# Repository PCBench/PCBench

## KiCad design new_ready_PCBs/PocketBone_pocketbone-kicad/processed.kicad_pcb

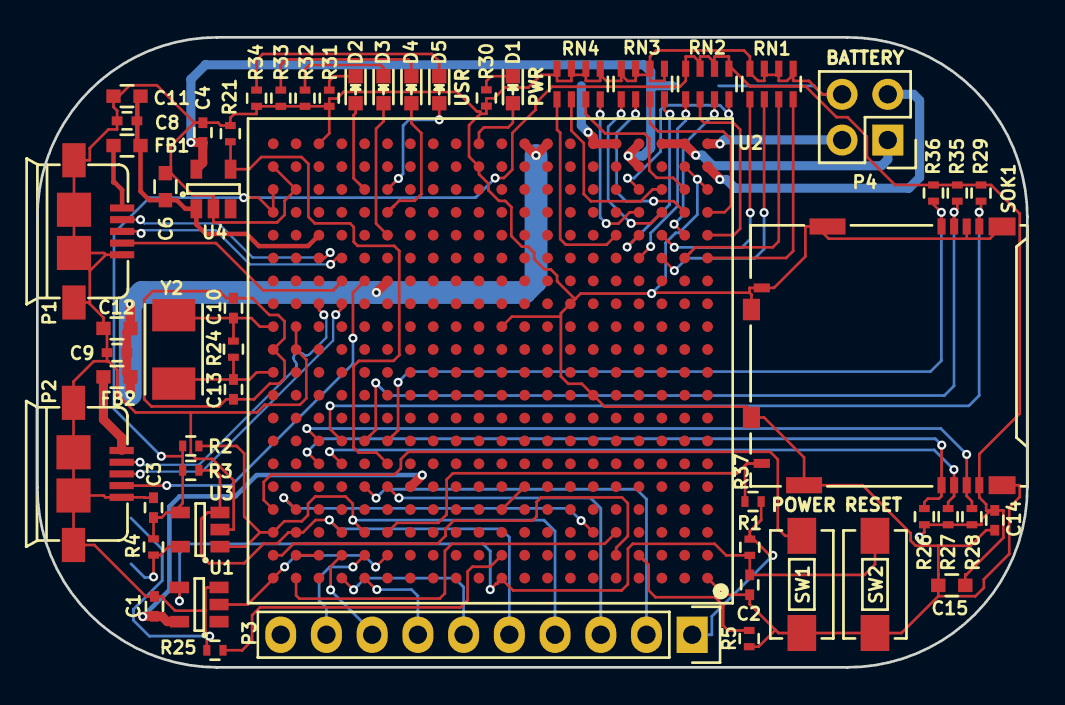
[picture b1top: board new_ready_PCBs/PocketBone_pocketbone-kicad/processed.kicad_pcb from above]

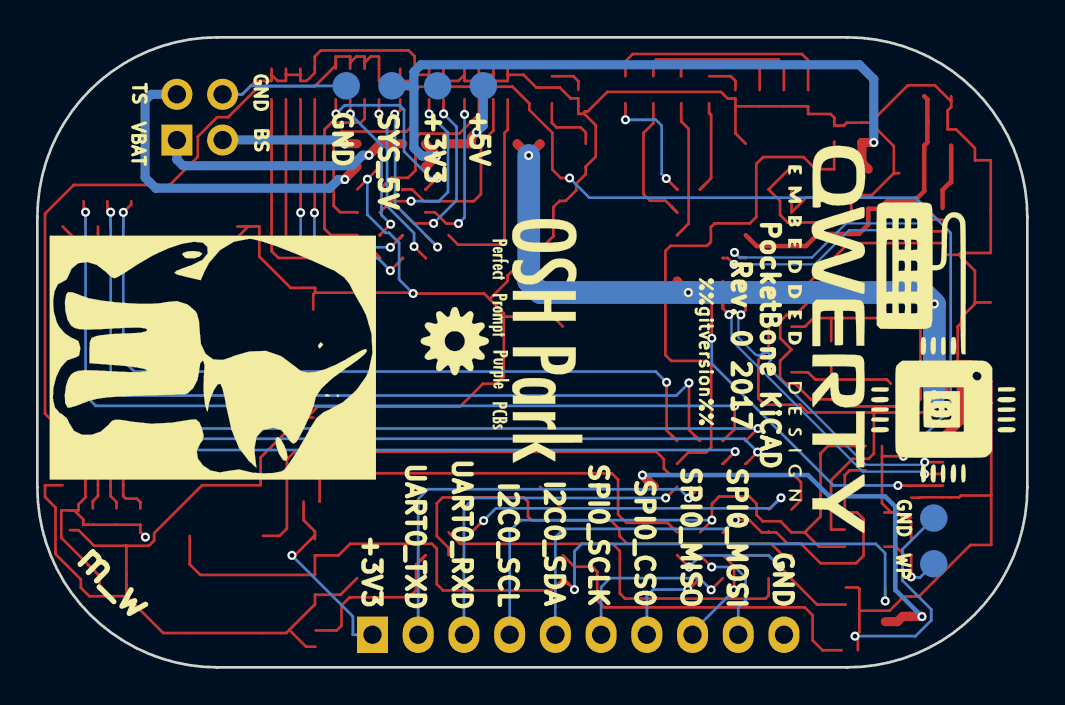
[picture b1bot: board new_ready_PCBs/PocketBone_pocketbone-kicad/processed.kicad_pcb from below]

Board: 4 copper layers, 55.0 x 35.0 mm, 62 parts (6 on the bottom side), 74 nets.

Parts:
C1, C3, C4, C8, C9, C14: 0.1uF; C_0402
C2: 1uF; C_0402
C6, C11, C12, C15: 10uF; C_0603
C10, C13: 18pF; C_0402
D1, D2, D3, D4, D5: BLUE; LED-0603
FB1, FB2: FILTER; C_0603
P1, P2: USB_OTG; USB_MICRO_B_ST-USB-001E
P3: CONN_01X10; Socket_Strip_Straight_1x10
P4: CONN_02X02; Socket_Strip_Straight_2x02
R1, R5, R26, R27, R28, R29, R35, R36, R37: 10K; R_0402
R2, R3, R4: 1.5K; R_0402
R21: 100K; R_0402
R24: 1M; R_0402
R25: 4.87K; R_0402
R30: 4.7K; R_0402
R31, R32, R33, R34: 240; R_0402
RN1, RN2, RN3, RN4: 100K; R_Array_Concave_4x0603
SOK1: SCHA5B0200
SW1, SW2: SW_PUSH_SMALL_H; SW_SPST_EVQPE1
TP1: 5V; Measurement_Point_Round-SMD-Pad_Small
TP2: WP; Measurement_Point_Round-SMD-Pad_Small
TP3, TP6: GND; Measurement_Point_Round-SMD-Pad_Small
TP4: 3P3; Measurement_Point_Round-SMD-Pad_Small
TP5: SYS_5V; Measurement_Point_Round-SMD-Pad_Small
U1: SN74LVC1G07; SOT-23-5
U2: OSD3358; BGA-400-1-27mm
U3: 24LC32AT-I/OT; SOT-23-5
U4: TPS2051C; SOT-23-5
Y2: 24MHz; 445C33D24M00000

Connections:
3P3AUX: D1.2, U2.Y11
+3V3: C3.1, C14.1, C15.1, P3.1, R1.1, R2.1, R3.1, R4.1, R26.1, R27.1, R28.1, R29.1, R35.1, R36.1, R37.1, RN2.5, RN2.6, RN2.7, RN2.8, SOK1.4, U2.U20, U2.V20, U3.4
+5V: TP1.1, U2.Y5, U2.Y6
BAT_SENSE: P4.3, U2.Y1
GND: C1.2, C2.2, C3.2, C4.2, C6.2, C8.2, C9.2, C11.2, C12.2, C14.2, C15.2, P1.5, P1.6, P1.7, P1.8, P1.9, P2.5, P2.6, P2.7, P2.8, P2.9, P3.10, P4.4, R5.2, R21.2, R25.1, R30.1, R31.1, R32.1, R33.1, R34.1, RN1.1, RN1.2, RN1.3, RN1.4, RN3.1, RN3.2, RN3.3, RN3.4, RN4.1, RN4.2, RN4.3, RN4.4, SOK1.6, SOK1.10, SOK1.11, SW1.1, SW2.1, TP3.1, TP6.1, U1.3, U2.A1, U2.J6, U2.L19, U2.M10, U2.M19, U2.N7, U2.V1, U2.V19, U2.W2, U2.W11, U2.W20, U2.Y18, U3.2, U4.2
I2C0_SCL: P3.4, R2.2, U2.C16, U2.C20, U3.1
I2C0_SDA: P3.5, R3.2, U2.C17, U2.C19, U3.3
MMC0_CD: R37.2, SOK1.9, U2.C15
MMC0_CLK: R29.2, SOK1.5, U2.G17
MMC0_CMD: R28.2, SOK1.3, U2.G18
MMC0_DAT0: R35.2, SOK1.7, U2.G16
MMC0_DAT1: R36.2, SOK1.8, U2.G15
MMC0_DAT2: R26.2, SOK1.1, U2.F18
MMC0_DAT3: R27.2, SOK1.2, U2.F17
unnamed: C2.1, R1.2, SW2.2, U1.4, U2.A10
unnamed: C10.1, R24.2, U2.M20, Y2.1
unnamed: C13.1, R24.1, U2.K20, Y2.2
unnamed: D1.1, R30.2
unnamed: D2.1, R31.2
unnamed: D3.1, R32.2
unnamed: D4.1, R33.2
unnamed: D5.1, R34.2
unnamed: FB1.2, P1.1
unnamed: FB2.2, P2.1
unnamed: R4.2, TP2.1, U3.5
unnamed: R5.1, U2.B4
unnamed: RN1.5, U2.T3
unnamed: RN1.6, U2.R3
unnamed: RN1.7, U2.R2
unnamed: RN1.8, U2.R1
unnamed: RN2.1, U2.R4
unnamed: RN2.2, U2.T1
unnamed: RN2.3, U2.T2
unnamed: RN2.4, U2.V4
unnamed: RN3.5, U2.U3
unnamed: RN3.6, U2.U2
unnamed: RN3.7, U2.U1
unnamed: RN3.8, U2.T4
unnamed: RN4.5, U2.T5
unnamed: RN4.6, U2.V3
unnamed: RN4.7, U2.V2
unnamed: RN4.8, U2.U4
unnamed: SW1.2, U2.D20
unnamed: U2.A19, U2.C5
unnamed: U2.B18, U2.B19
unnamed: U2.B5, U2.B20
unnamed: U2.C6, U2.D19
OSC0_GND: C10.2, C13.2, U2.L20
PMIC_PGOOD: U1.2, U2.A20, U2.B15
SPI_CLK: P3.6, U2.A17
SPI_CS0: P3.7, U2.A16
SPI_MISO: P3.8, U2.B17
SPI_MOSI: P3.9, U2.B16
SYS_5V: C4.1, TP5.1, U2.W4, U2.Y4, U4.5
TRSTN: R25.2, U2.B10
TS: P4.2, U2.W1
UART0_RXD: P3.3, U2.E15
UART0_TXD: P3.2, U2.E16
USB0_D_N: P2.2, U2.N18
USB0_D_P: P2.3, U2.N17
USB0_ID: P2.4, U2.P16
USB0_VBUS: C9.1, C12.1, FB2.1, U2.P15, U2.Y8, U2.Y9
USB1_DRVVBUS: R21.1, U2.F15, U4.4
USB1_D_N: P1.2, U2.R18
USB1_D_P: P1.3, U2.R17
USB1_ID: P1.4, U2.P17
USB1_VBUS: C6.1, C8.1, C11.1, FB1.1, U2.T18, U4.1
USR0_LED: D5.2, U2.V15
USR1_LED: D4.2, U2.U15
USR2_LED: D3.2, U2.T15
USR3_LED: D2.2, U2.V16
VBAT: P4.1, U2.Y2, U2.Y3
VDD_1V8: U2.D10, U2.E9
VDD_RTC: C1.1, U1.5, U2.E14

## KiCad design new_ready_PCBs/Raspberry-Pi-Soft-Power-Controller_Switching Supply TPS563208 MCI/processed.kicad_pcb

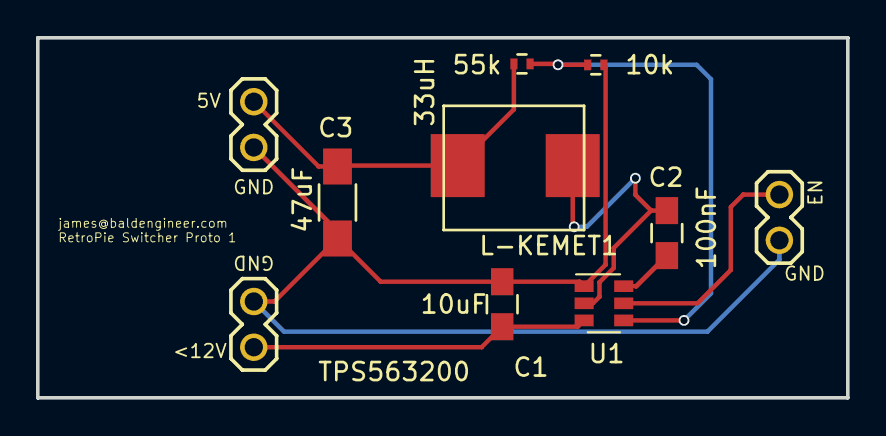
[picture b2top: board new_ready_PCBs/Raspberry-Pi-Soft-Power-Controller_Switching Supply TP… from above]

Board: 2 copper layers, 45.0 x 20.0 mm, 10 parts (0 on the bottom side), 7 nets.

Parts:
C1: 10uF; C_0805_HandSoldering
C2: 100nF; C_0805_HandSoldering
C3: 47uF; C_1206_HandSoldering
J1: 9V-IN; 1X02
J2: EN; 1X02
J3: 5V-OUT; 1X02
L-KEMET1: 33uH; KT-MPLCH-0740-Hand
R1: 55k; R_0402
R2: 10k; R_0402
U1: TPS563200; SOT-23-6

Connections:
/ENABLE: J2.2, U1.5
/IN: C1.1, J1.2, U1.3
/OUT: C3.2, J3.1, L-KEMET1.2, R1.1
/ToCoil: C2.1, L-KEMET1.1, U1.2
GND: C1.2, C3.1, J1.1, J2.1, J3.2, R2.2, U1.1
unnamed: C2.2, U1.6
unnamed: R1.2, R2.1, U1.4

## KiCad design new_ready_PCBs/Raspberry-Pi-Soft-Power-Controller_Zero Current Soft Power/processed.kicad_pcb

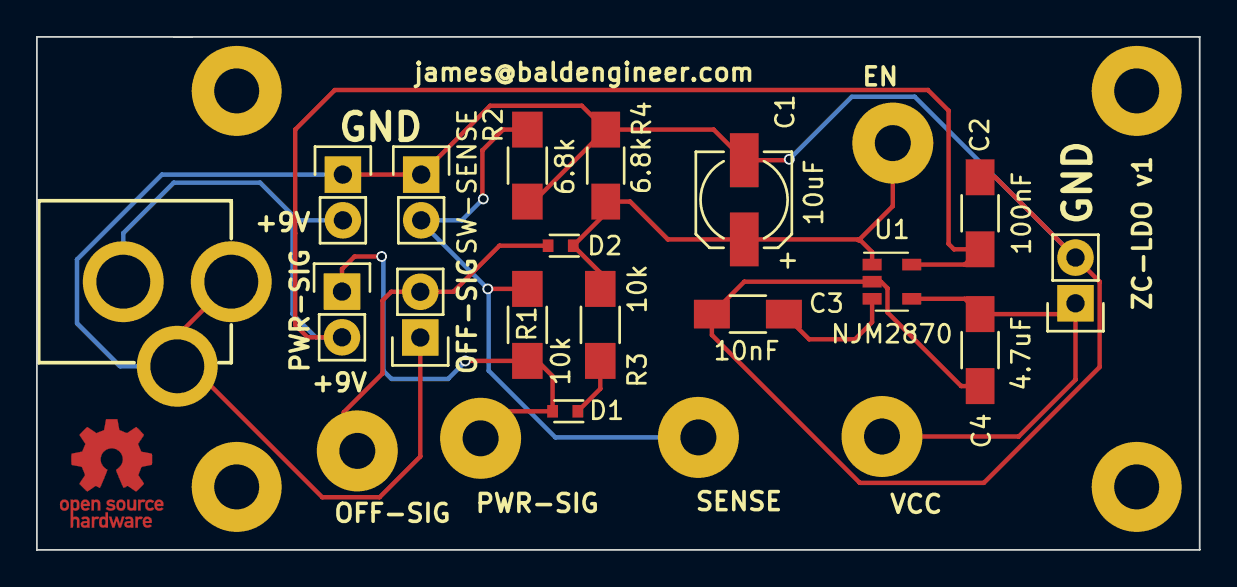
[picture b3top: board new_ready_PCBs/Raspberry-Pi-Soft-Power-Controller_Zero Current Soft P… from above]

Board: 2 copper layers, 64.6 x 28.5 mm, 22 parts (0 on the bottom side), 9 nets.

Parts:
C1: 10uF; c_elec_5x5.3
C2: 100nF; C_1206_HandSoldering
C3: 10nF; C_1206_HandSoldering
C4: 4.7uF; C_1206_HandSoldering
D1, D2: 1SS389; SOD-523
J1: PWR-SIG; Pin_Header_Straight_1x02
J2: SW-SENSE; Pin_Header_Straight_1x02
J3: 9V-IN; Pin_Header_Straight_1x02
J4: SENSE; SolderWirePad_single_2mmDrill
J5: OFF-SIG; Pin_Header_Straight_1x02
J6: TEST_1P; SolderWirePad_single_2mmDrill
J7: OFF-SIG; SolderWirePad_single_2mmDrill
J8: EN; SolderWirePad_single_2mmDrill
J9: VCC; SolderWirePad_single_2mmDrill
J10: AVR-VCC; Pin_Header_Straight_1x02
J11: 9V-BJ; POWER_JACK_PTH
R1, R3: 10k; R_1206_HandSoldering
R2: 6.8k; R_1206_HandSoldering
R4: 6.8k; C_1206_HandSoldering
U1: NJM2870; SOT-23-5

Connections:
+9V: C2.1, J1.2, J3.2, J11.1, U1.5
/LC-VCC: C4.1, J9.1, J10.1, U1.4
/OFF-SIG: D2.2, J5.2, J7.1
/PWR-SIG: D1.2, J1.1, J6.1, R1.2
/SW-SENSE: J2.2, J4.1, R1.1, R2.2
GND: C1.2, C2.2, C3.2, C4.2, J2.1, J3.1, J5.1, J10.2, J11.2, J11.3, R2.1, R4.1, U1.2
unnamed: C1.1, D2.1, J8.1, R3.1, R4.2, U1.1
unnamed: C3.1, U1.3
unnamed: D1.1, R3.2

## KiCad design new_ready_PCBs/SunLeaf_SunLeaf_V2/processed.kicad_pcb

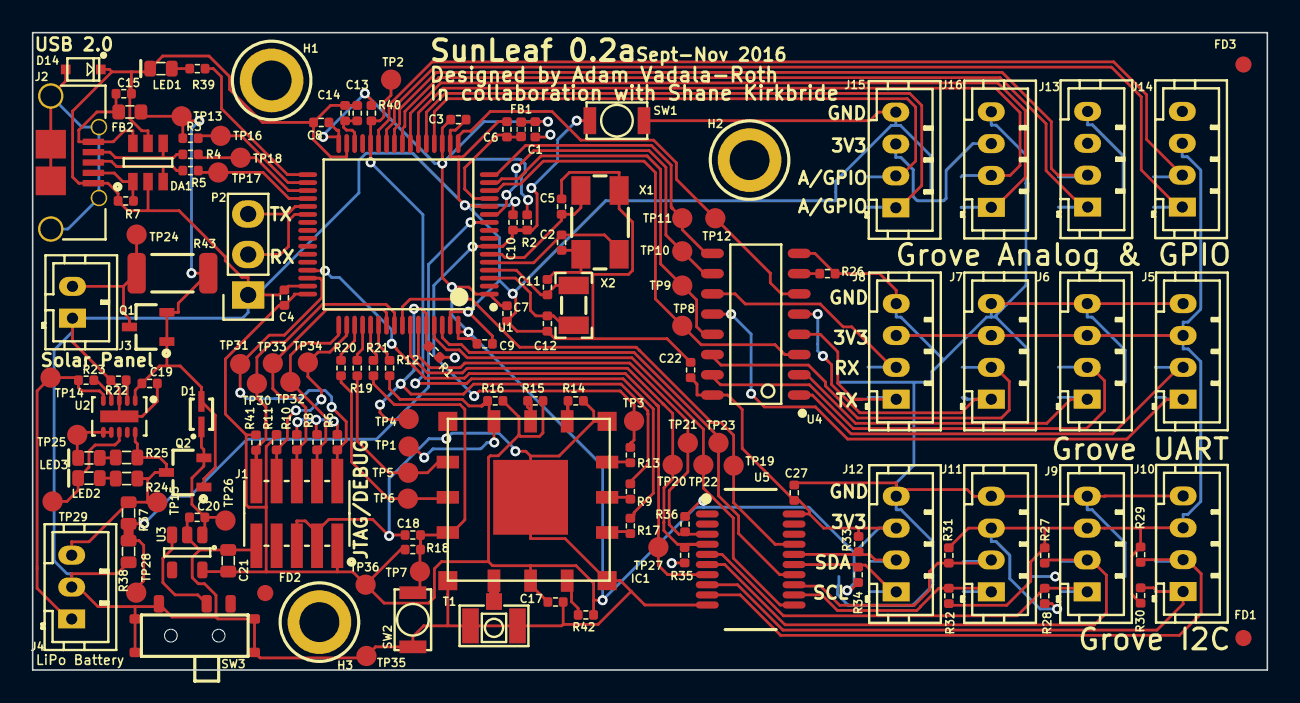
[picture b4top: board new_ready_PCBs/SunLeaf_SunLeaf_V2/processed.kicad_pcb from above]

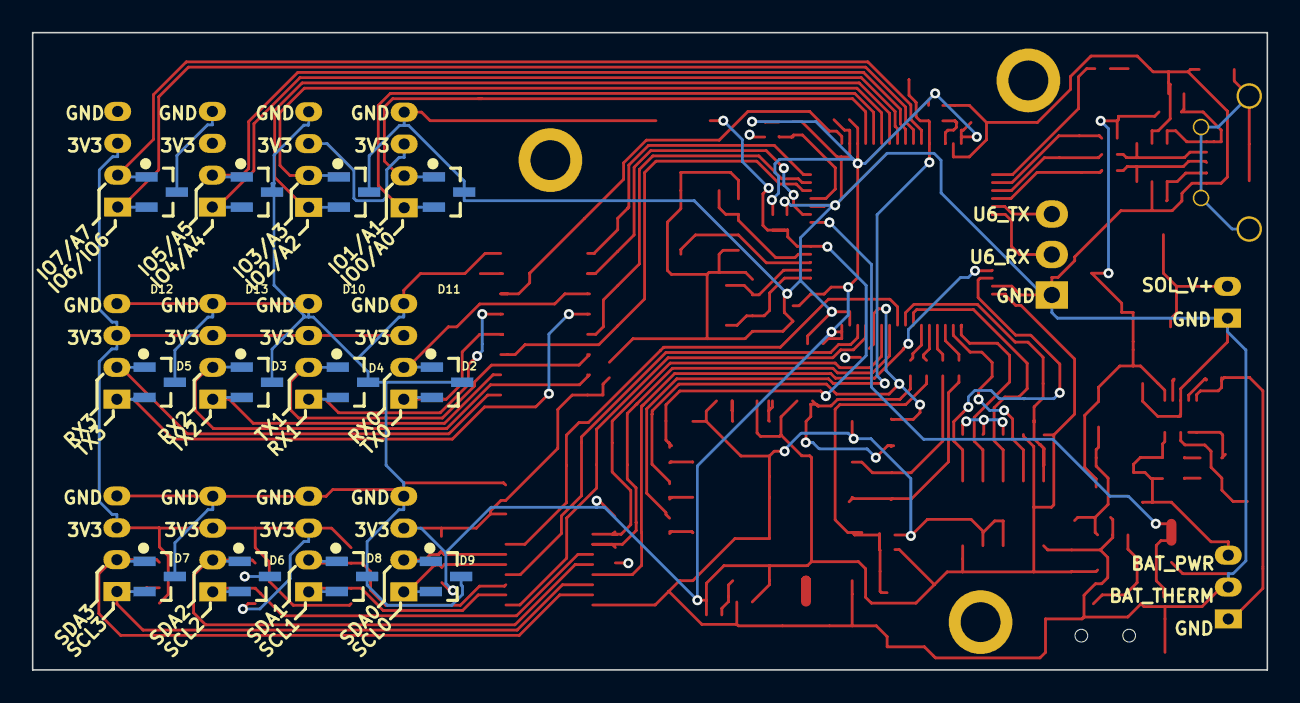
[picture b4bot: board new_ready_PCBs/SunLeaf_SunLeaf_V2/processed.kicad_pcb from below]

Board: 4 copper layers, 77.5 x 40.0 mm, 158 parts (12 on the bottom side), 92 nets.

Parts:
C1, C3, C4, C6, C7, C8, C9, C10, C14, C15, C17, C18, C22, C27: CL05B104JP5NNNC; C0402
C2, C5: CL05C090CB5NNNC; C0402
C11, C12: CL05C180GB5NCNC; C0402
C13: CL05A475KQ5NRNC; C0402
C19, C20: CL05A105KA5NQNC; C0402
C21: CL10A106KQ8NNNC; C0603
D1: BAT20JFILM
D2, D3, D4, D5, D6, D7, D8, D9, D10, D11, D12, D13: PESD3V3L2BT,215
D14: RSB39VTE-17
DA1: ESDA6V1BC6
FB1: BLM15HG601SN1D
FB2: MI0603K300R-10
FD1, FD2, FD3: FIDUCIAL
H1, H2, H3: M2.5_Hole; M2.5_HOLE
IC1: ESP_09; ESP-09
J1: 20021121-00010C4LF
J2: 0475890001-MicroUSBPort; 0475890001
J3: B2B-PH-K-S(LF)(SN)
J4: B3B-PH-K-S(LF)(SN)
J5, J6, J7, J8, J9, J10, J11, J12, J13, J14, J15, J16: B4B-PH-K-S(LF)(SN)
LED1: LTST-C193TBKT-5A; LED0603
LED2: LTST-C191KGKT; LED0603
LED3: LTST-C191KFKT; LED0603
P2: CONN_01X03; Pin_Header_Straight_1x03
Q1, Q2: DMG2307L-7
R1, R3, R14, R15, R16, R40, R42: RC1005F103CS; R0402
R2, R6, R8, R10, R11, R18, R23, R26, R39, R41: RC1005F102CS; R0402
R4, R5: CPF0402B22RE1; R0402
R7: RC1005J473CS; R0402
R9, R12, R13, R17, R19, R20, R21: RC1005F201CS; R0402
R22: RC1005F4870CS; R0402
R24, R25: RC1608J202CS; R0603
R27, R28, R29, R30, R31, R32, R33, R34, R35, R36: RC1005F472CS; R0402
R37, R38: ERA-3AEB3741V; R0603
R43: RC5025J000CS; R2010
SW1, SW2: B3U-1000P
SW3: CUS-12TB
T1: 1909763-1
TP1, TP2, TP3, TP4, TP5, TP6, TP7, TP8, TP9, TP10, TP11, TP12, TP13, TP14, TP15, TP16, TP17, TP18, TP19, TP20, TP21, TP22, TP23, TP24, TP25, TP26, TP27, TP28, TP29, TP30, TP31, TP32, TP33, TP34, TP35, TP36: TEST_POINT
U1: STM32F446RET6_-_TQFP64; STM32F446RET6
U2: BQ24210DQCT; BQ24210
U3: AP2112K-3.3TRG1
U4: 74HC4052D
U5: PCA9518DBQR
X1: ABM3B8.000MHZB2T
X2: ABS07-32.768KHZ-9-T

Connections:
+3V3: C1.1, C3.1, C4.1, C7.1, C8.1, C9.1, C17.1, C21.1, C22.1, C27.1, FB1.1, IC1.15, J1.1, J5.3, J6.3, J7.3, J8.3, J9.3, J10.3, J11.3, J12.3, J13.3, J14.3, J15.3, J16.3, R2.1, R6.1, R8.1, R10.1, R11.1, R15.1, R16.1, R18.1, R27.1, R28.1, R29.1, R30.1, R31.1, R32.1, R33.1, R34.1, R35.1, R36.1, R40.1, R41.1, R42.2, TP36.1, U1.1, U1.19, U1.32, U1.48, U1.64, U3.5, U4.16, U5.20
/Analog and Digital Grove IO/ANIO_0: D13.1, J13.2, U1.25
/Analog and Digital Grove IO/ANIO_1: D13.2, J13.1, U1.24
/Analog and Digital Grove IO/ANIO_2: D12.1, J14.2, U1.27
/Analog and Digital Grove IO/ANIO_3: D12.2, J14.1, U1.26
/Analog and Digital Grove IO/ANIO_4: D11.1, J15.2, U1.20
/Analog and Digital Grove IO/ANIO_5: D11.2, J15.1, U1.21
/Analog and Digital Grove IO/ANIO_6: D10.1, J16.2, U1.22
/Analog and Digital Grove IO/ANIO_7: D10.2, J16.1, U1.23
/I2C Grove Sensors/EN1_IMUX: TP27.1, U1.45, U5.7
/I2C Grove Sensors/EN2_IMUX: TP22.1, U1.61, U5.11
/I2C Grove Sensors/EN3_IMUX: TP23.1, U1.62, U5.14
/I2C Grove Sensors/EN4_IMUX: TP19.1, U1.57, U5.17
/I2C Grove Sensors/I2C_SCL: R35.2, TP20.1, U1.58, U5.4
/I2C Grove Sensors/I2C_SDA: R36.2, TP21.1, U1.59, U5.3
/MCU-STM32F446RET6/BAT_VOLT: R37.2, R38.1, TP28.1, U1.10
/MCU-STM32F446RET6/ESPTOST_BOOT0: R1.1, R9.1, TP4.1, U1.60
/MCU-STM32F446RET6/ESPTOST_BOOT1: R17.1, R40.2, TP2.1, U1.28
/MCU-STM32F446RET6/ESP_PGM_MODE: R12.1, U1.54
/MCU-STM32F446RET6/ESP_ST_RST: C10.1, R2.2, R13.1, SW1.1, TP3.1, U1.7
/MCU-STM32F446RET6/ESP_URX: R19.2, U1.52
/MCU-STM32F446RET6/ESP_UTX: R20.2, U1.51
/MCU-STM32F446RET6/HEARTBEAT: R39.1, U1.33
/MCU-STM32F446RET6/NJTRST: J1.10, R41.2, TP30.1, U1.56
/MCU-STM32F446RET6/STM_ESP_RST: R21.2, U1.53
/MCU-STM32F446RET6/SWCLK_TCK: J1.4, R8.2, TP32.1, U1.49
/MCU-STM32F446RET6/SWDIO_TMS: J1.2, R6.2, TP31.1, U1.46
/MCU-STM32F446RET6/SWO_TDI: J1.8, R11.2, TP34.1, U1.50
/MCU-STM32F446RET6/SWO_TDO: J1.6, R10.2, TP33.1, U1.55
/MCU-STM32F446RET6/UART6_RX: P2.2, U1.38
/MCU-STM32F446RET6/UART6_TX: P2.3, U1.37
/MCU-STM32F446RET6/UART_S_RX: TP9.1, U1.15, U4.13
/MCU-STM32F446RET6/USW_EN: TP12.1, U1.17, U4.6
/MCU-STM32F446RET6/USW_S0: TP10.1, U1.11, U4.10
/MCU-STM32F446RET6/USW_S1: TP11.1, U1.16, U4.9
/MCU-STM32F446RET6/VBUS: C19.1, D1.1, FB2.1, Q1.1, Q1.2, Q2.1, R3.2, R43.2, TP13.1, U2.1
/Power-System/BAT: J4.3, Q2.3, R24.2, R25.2, R37.1, TP15.1, U2.10
/Power-System/THERM: J4.1, R23.2, TP14.1, U2.5
/UART Grove Sensors/UART_RX0: D5.1, J5.2, U4.1
/UART Grove Sensors/UART_RX1: D4.1, J6.2, U4.14
/UART Grove Sensors/UART_RX2: D3.1, J7.2, U4.15
/UART Grove Sensors/UART_RX3: D2.1, J8.2, U4.11
/UART Grove Sensors/UART_S_RX: TP8.1, U1.14, U4.3
/UART Grove Sensors/UART_TX0: D5.2, J5.1, U4.12
/UART Grove Sensors/UART_TX1: D4.2, J6.1, U4.5
/UART Grove Sensors/UART_TX2: D3.2, J7.1, U4.2
/UART Grove Sensors/UART_TX3: D2.2, J8.1, U4.4
/WiFi-ESP8266-ESP-09/ANTENNA: IC1.14, T1.1
/WiFi-ESP8266-ESP-09/PGM_MODE: IC1.8, R12.2, R16.2, TP1.1
GND: C1.2, C2.2, C3.2, C4.2, C5.2, C6.2, C7.2, C8.2, C9.2, C10.2, C11.2, C12.2, C13.2, C14.2, C15.1, C17.2, C18.2, C19.2, C20.2, C21.2, C22.2, C27.2, D2.3, D3.3, D4.3, D5.3, D7.3, D8.3, D9.3, D10.3, D11.3, D12.3, D13.3, D14.2, DA1.2, DA1.5, IC1.1, IC1.5, IC1.9, IC1.13, IC1.17, J1.3, J1.5, J1.9, J2.5, J3.1, J4.2, J5.4, J6.4, J7.4, J8.4, J9.4, J10.4, J11.4, J12.4, J13.4, J14.4, J15.4, J16.4, LED1.2, P2.1, R1.2, R7.2, R14.2, R22.2, R26.1, R38.2, SW1.2, SW2.2, SW3.1, SW3.4, T1.2, TP35.1, U1.12, U1.18, U1.31, U1.47, U1.63, U2.3, U2.11, U3.2, U4.8, U5.10, X1.2, X1.4
unnamed: C2.1, U1.5, X1.1
unnamed: C5.1, U1.6, X1.3
unnamed: C6.1, FB1.2, U1.13
unnamed: C11.1, U1.4, X2.1
unnamed: C12.1, U1.3, X2.2
unnamed: C13.1, C14.1, U1.30
unnamed: C15.2, DA1.6, FB2.2, J2.1
unnamed: C18.1, IC1.12, R18.2, R21.1, SW2.1, TP7.1
unnamed: C20.1, D1.2, Q2.2, TP26.1, U3.1
unnamed: D6.1, J9.2, R27.2, U5.6
unnamed: D6.2, J9.1, R28.2, U5.5
unnamed: D7.1, J10.2, R29.2, U5.9
unnamed: D7.2, J10.1, R30.2, U5.8
unnamed: D8.1, J11.2, R31.2, U5.13
unnamed: D8.2, J11.1, R32.2, U5.12
unnamed: D9.1, J12.2, R33.2, U5.16
unnamed: D9.2, J12.1, R34.2, U5.15
unnamed: D14.1, J2.6, J2.7, J2.8, J2.9, J2.10, J2.11
unnamed: DA1.1, J2.4, R7.1
unnamed: DA1.3, J2.3, R5.2
unnamed: DA1.4, J2.2, R4.2
unnamed: IC1.2, R17.2
unnamed: IC1.3, R9.2
unnamed: IC1.4, R13.2
unnamed: IC1.6, R14.1
unnamed: IC1.7, R15.2
unnamed: IC1.10, R19.1, TP5.1
unnamed: IC1.11, R20.1, TP6.1
unnamed: IC1.16, R42.1
unnamed: J3.2, Q1.3, R43.1, TP24.1
unnamed: LED1.1, R39.2
unnamed: LED2.1, R24.1
unnamed: LED2.2, TP29.1, U2.8
unnamed: LED3.1, R25.1
unnamed: LED3.2, TP25.1, U2.6, U2.7
unnamed: R3.1, TP16.1, U1.34
unnamed: R4.1, TP18.1, U1.35
unnamed: R5.1, TP17.1, U1.36
unnamed: R22.1, U2.2
unnamed: R23.1, U2.4
unnamed: R26.2, U4.7
unnamed: SW3.2, U3.3

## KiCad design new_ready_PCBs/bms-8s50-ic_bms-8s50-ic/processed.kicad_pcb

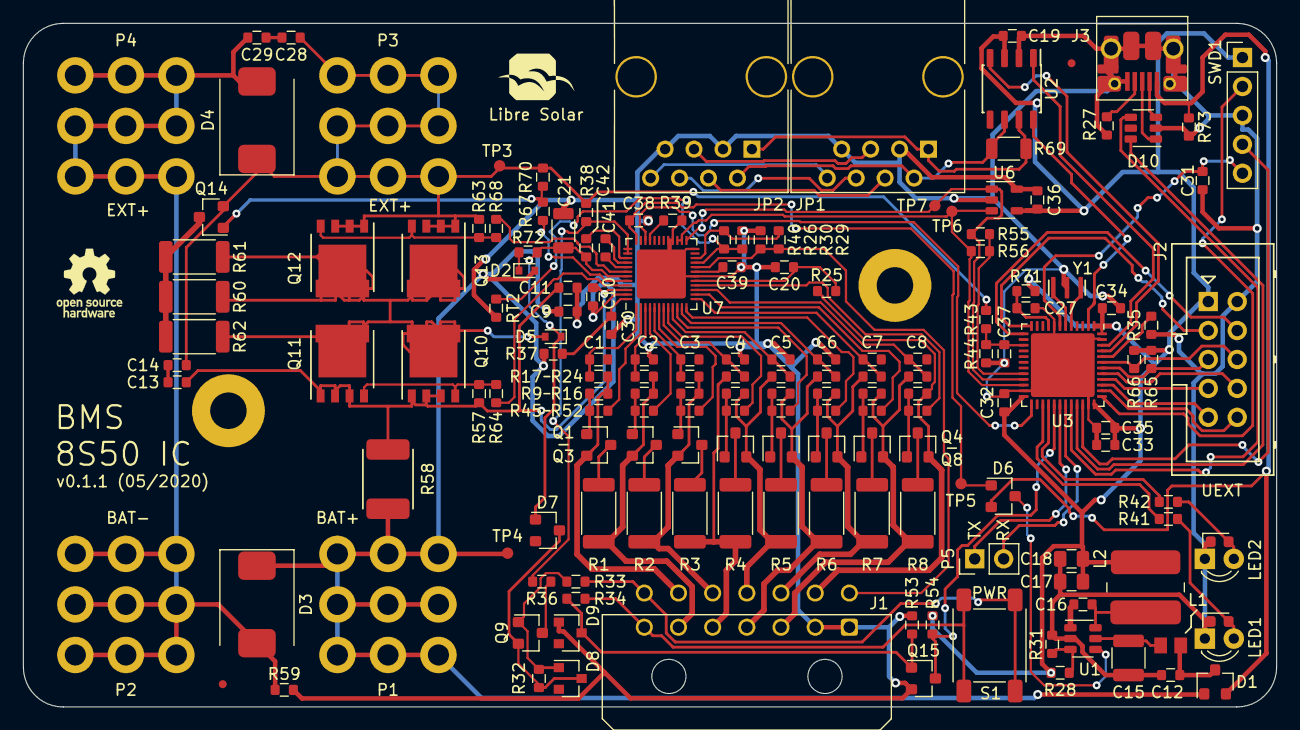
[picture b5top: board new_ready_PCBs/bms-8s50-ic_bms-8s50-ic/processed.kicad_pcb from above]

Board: 2 copper layers, 110.0 x 60.0 mm, 166 parts (0 on the bottom side), 125 nets.

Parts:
C1, C2, C3, C4, C5, C6, C7, C8, C20: 47n; C_0603_1608
C9, C11, C12, C39: 1u; C_0603_1608
C10: 10n; C_0603_1608
C13, C14, C16, C19, C27, C28, C29, C31, C32, C33, C34, C36, C38: 100n; C_0603_1608
C15: 4.7u; C_1210_3225
C17, C18: 10u; C_0805_2012
C21: 4.7u; C_1206_3216
C30: 470n; C_0603_1608
C35: 4.7u; C_0603_1608
C37, C41, C42: 4.7n; C_0603_1608
D1, D6, D7: BAV70; SOT-23
D2, D5: PMEG6002; D_SOD-523
D3, D4: SMCJ36A; D_SMC
D8, D9: 12V; D_SOT-23_ANK
D10: USBLC6-2SC6; SOT-23-6
H1, H2: MountingHole; MountingHole_3.2mm_M3_Pad
J1: Conn_01x10; Molex_Micro-Fit_3.0_43045-1400_2x07_P3.00mm_Horizontal
J2: UEXT; Box_Header_2x05x2.54mm_Straight
J3: USB_B_Micro; USB_Micro-B_10103594-0001LF
JP1, JP2: RJ45_NS; RJ45_8P8C
L1: 4.7uH; L_0805_2012Metric
L2: 47uH; Bourns_SRN6045TA
LED1, LED2: LED; LED_0603_D3.0mm
LOGO1: OPEN_HARDWARE; OSHW-Logo_5.7x6mm_SilkScreen
LOGO2: LIBRE_SOLAR; LIBRESOLAR_LOGO
P1, P2, P3, P4: CONN_01X01; Wuerth_WP-THRBU_74650195
P5: CONN_01X02; PinHeader_1x02_P2.54mm_Vertical
Q1, Q2, Q3, Q9: NDS0605; SOT-23
Q4, Q5, Q6, Q7, Q8, Q14, Q15: BSS138; SOT-23
Q10, Q11, Q12, Q13: BSC016N06NS; 5X6_MOSFET
R1, R2, R3, R4, R5, R6, R7, R8: 33; R_2010_5025
R9, R10, R11, R12, R13, R14, R15, R16, R27, R43, R73: 330k; R_0603_1608
R17, R18, R19, R20, R21, R22, R23, R24, R25, R36, R38, R41, R42, R54: 1k; R_0603_1608
R26, R30, R33, R34, R45, R46, R47, R48, R49, R50, R51, R52: 10k; R_0603_1608
R28: 50.5k; R_0603_1608
R29, R31, R40, R44: 22k; R_0603_1608
R32, R35, R53, R57, R63, R70: 1M; R_0603_1608
R37, R59, R64, R67, R68, R71: 100; R_0603_1608
R39, R55, R56, R65, R66: 2.2k; R_0603_1608
R58: 1m; R_Shunt_2512
R60, R61, R62: 330; R_2010_5025
R69: 120; R_1206_3216
R72: 4R7; R_0603_1608
RT2: 10k; R_0603_1608
S1: SW_PUSH; SW_SPST_6mm
SWD1: ST_Nucleo_SWD_5p; PinHeader_1x05_P2.54mm_Vertical
TP3: Ext+; TestPoint_1mm_pad
TP4: Bat+; TestPoint_1mm_pad
TP5: Regout; TestPoint_1mm_pad
TP6: SDA; TestPoint_1mm_pad
TP7: SCL; TestPoint_1mm_pad
U1: TPS560430X; SOT-23-6
U2: TCAN334; SOIC-8_3.9x4.9mm_Pitch1.27mm
U3: STM32F072CBU6; QFN-48-1EP_7x7mm_P0.5mm_EP5.6x5.6mm
U6: 24AA32; SOT-23-5
U7: ISL94202; QFN-48-1EP_6x6mm_P0.4mm_EP4.3x4.3mm
Y1: 8MHz; Resonator_Murata_CSTNE

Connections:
+3V3: C17.1, C18.1, C19.1, C32.1, C33.1, C34.1, C35.1, C36.1, J2.1, L2.2, R28.1, R54.2, R65.2, R66.2, R71.2, SWD1.1, U2.3, U3.1, U3.24, U3.36, U3.48, U6.4
+5V: D1.2, D6.2, J3.1, R73.1
/BAT+: C9.1, C10.1, D1.1, D2.2, D3.1, P1.1, R37.1, R58.2, TP4.1, U7.47
/BAT-: C29.2, D3.2, D4.2, P2.1, P4.1, R59.1
/CAN_V+: JP1.8, JP2.8
/EXT+: C14.2, C28.1, D4.1, P3.1, Q12.S, Q13.S, Q14.2, R38.1, R43.1, R63.1, R70.1, TP3.1
/ISL94202/ALERT: U3.25, U7.34
/ISL94202/BTN_1: J1.14, R33.1, S1.2
/ISL94202/BTN_2: J1.7, R34.2, S1.1
/ISL94202/BTN_SIGNAL: Q15.3, R54.1, U3.29
/ISL94202/CB1: R52.1, U7.16
/ISL94202/CB2: R51.1, U7.14
/ISL94202/CB3: R50.1, U7.12
/ISL94202/CB4: R49.1, U7.10
/ISL94202/CB5: R48.1, U7.8
/ISL94202/CB6: R47.1, U7.6
/ISL94202/CB7: R46.1, U7.4
/ISL94202/CB8: R45.1, U7.2
/ISL94202/CELL1+: J1.3, Q7.2, R8.2, R15.1, R24.2
/ISL94202/CELL1-: J1.9, Q8.2, R16.1, R25.2
/ISL94202/CELL2+: J1.10, Q6.2, R7.2, R14.1, R23.2
/ISL94202/CELL3+: J1.4, Q5.2, R6.2, R13.1, R22.2
/ISL94202/CELL4+: J1.11, Q4.2, R5.2, R12.1, R21.2
/ISL94202/CELL5+: J1.5, R3.1, R4.2, R20.2
/ISL94202/CELL6+: J1.12, Q3.2, R2.1, R11.2, R19.2
/ISL94202/CELL7+: J1.6, Q2.2, R1.1, R10.2, R18.2
/ISL94202/CELL8+: J1.13, Q1.2, R9.2, R17.2
/ISL94202/CFET: R64.2, U7.45
/ISL94202/CHG+: D5.2, Q10.D, Q11.D, Q12.D, Q13.D, R60.2, R61.2, R62.2
/ISL94202/CHMON: R36.1, R38.2, U7.37, U7.38
/ISL94202/CSI2: C10.2, C11.1, C13.1, Q10.S, Q11.S, R57.2, R58.1, U7.46
/ISL94202/DFET: R68.1, U7.42
/ISL94202/NTC_BAT: J1.8, R29.1, R30.2, U7.20
/ISL94202/PCFET: R67.2, U7.44
/ISL94202/RGO: C38.1, D6.1, TP5.1, U7.36
/ISL94202/TEMPO: R29.2, R40.2, U7.22
/ISL94202/VC0: C20.1, R25.1, U7.17
/ISL94202/VC1: C8.1, R24.1, U7.15
/ISL94202/VC2: C7.1, R23.1, U7.13
/ISL94202/VC3: C6.1, R22.1, U7.11
/ISL94202/VC4: C5.1, R21.1, U7.9
/ISL94202/VC5: C4.1, R20.1, U7.7
/ISL94202/VC6: C3.1, R19.1, U7.5
/ISL94202/VC7: C2.1, R18.1, U7.3
/ISL94202/VC8: C1.1, R17.1, U7.1
/ISL94202/VDD: C21.1, C42.1, D5.1, D7.1, R72.1, U7.43
/ISL94202/XT2: R26.2, R40.1, RT2.1, U7.21
/MCU/BOOT0: R35.2, U3.44
/MCU/CAN_H: JP1.1, JP2.1, R69.1, U2.7
/MCU/CAN_L: JP1.2, JP2.2, R69.2, U2.6
/MCU/CAN_RX: U2.4, U3.45
/MCU/CAN_STB: U2.8, U3.2
/MCU/CAN_TX: U2.1, U3.46
/MCU/I2C1_SCL: J2.5, R65.1, U3.42
/MCU/I2C1_SDA: J2.6, R66.1, U3.43
/MCU/I2C2_PULLUP: R55.2, R56.2, U3.20
/MCU/I2C2_SCL: R55.1, TP7.1, U3.21, U6.1, U7.25
/MCU/I2C2_SDA: R56.1, TP6.1, U3.22, U6.3, U7.26, U7.27
/MCU/LED1: R41.2, U3.27
/MCU/LED2: R42.2, U3.28
/MCU/SPI1_MISO: J2.7, U3.40
/MCU/SPI1_MOSI: J2.8, U3.41
/MCU/SPI1_SCK: J2.9, U3.39
/MCU/SSEL: J2.10, U3.38
/MCU/SWCLK: SWD1.2, U3.37
/MCU/SWDIO: SWD1.4, U3.34
/MCU/USART1_RX: P5.2, U3.31
/MCU/USART1_TX: P5.1, U3.30
/MCU/USART2_RX: J2.4, U3.13
/MCU/USART2_TX: J2.3, U3.12
/MCU/USB_D+: D10.1, J3.3
/MCU/USB_D-: D10.3, J3.2
/MCU/USB_DM: D10.4, U3.32
/MCU/USB_DP: D10.6, U3.33
/MCU/~RESET: C31.1, SWD1.5, U3.7
/Power Supply/EN: D6.3, U1.4
/Power Supply/FB: R28.2, R31.1, U1.3
/Power Supply/SW: C16.2, L2.1, U1.6
/Power Supply/VIN: C15.1, L1.2, U1.5
/V_EXT: C37.1, R43.2, R44.1, U3.15
GND: C2.2, C4.2, C5.2, C6.2, C9.2, C11.2, C12.2, C15.2, C17.2, C18.2, C19.2, C20.2, C21.2, C27.2, C30.2, C31.2, C32.2, C33.2, C34.2, C35.2, C36.2, C37.2, C38.2, C39.2, D9.2, D10.2, J1.1, J1.2, J2.2, J3.5, J3.6, JP1.3, JP1.7, JP2.3, JP2.7, LED1.1, LED2.1, Q15.2, R26.1, R27.2, R30.1, R31.2, R35.1, R39.2, R44.2, R53.1, R59.2, R73.2, RT2.2, SWD1.3, U1.2, U2.2, U3.8, U3.23, U3.35, U3.47, U3.49, U6.2, U6.5, U7.18, U7.24, U7.28, U7.29, U7.49, Y1.2
unnamed: C12.1, D1.3, L1.1
unnamed: C13.2, C14.1
unnamed: C16.1, U1.1
unnamed: C27.1, R71.1, U3.9
unnamed: C28.2, C29.1
unnamed: C30.1, R37.2, U7.48
unnamed: C39.1, U7.19
unnamed: C41.1, U7.41
unnamed: C41.2, U7.40
unnamed: C42.2, U7.39
unnamed: D2.1, R72.2
unnamed: D7.3, D8.1, Q9.2, R32.2
unnamed: D8.2, Q9.1, R32.1, R33.2
unnamed: D9.1, Q15.1, R34.1, R53.2
unnamed: J3.4, R27.1
unnamed: JP1.4, JP2.4
unnamed: JP1.5, JP2.5
unnamed: JP1.6, JP2.6
unnamed: LED1.2, R41.1
unnamed: LED2.2, R42.1
unnamed: Q1.1, R9.1, R45.2
unnamed: Q1.3, R1.2
unnamed: Q2.1, R10.1, R46.2
unnamed: Q2.3, R2.2
unnamed: Q3.1, R11.1, R47.2
unnamed: Q3.3, R3.2
unnamed: Q4.1, R12.2, R48.2
unnamed: Q4.3, R4.1
unnamed: Q5.1, R13.2, R49.2
unnamed: Q5.3, R5.1
unnamed: Q6.1, R14.2, R50.2
unnamed: Q6.3, R6.1
unnamed: Q7.1, R15.2, R51.2
unnamed: Q7.3, R7.1
unnamed: Q8.1, R16.2, R52.2
unnamed: Q8.3, R8.1
unnamed: Q9.3, R36.2
unnamed: Q10.G, Q11.G, R57.1, R64.1
unnamed: Q12.G, Q13.G, R63.2, R68.2
unnamed: Q14.1, R67.1, R70.2
unnamed: Q14.3, R60.1, R61.1, R62.1
unnamed: R39.1, U7.33
unnamed: U3.5, Y1.3
unnamed: U3.6, Y1.1

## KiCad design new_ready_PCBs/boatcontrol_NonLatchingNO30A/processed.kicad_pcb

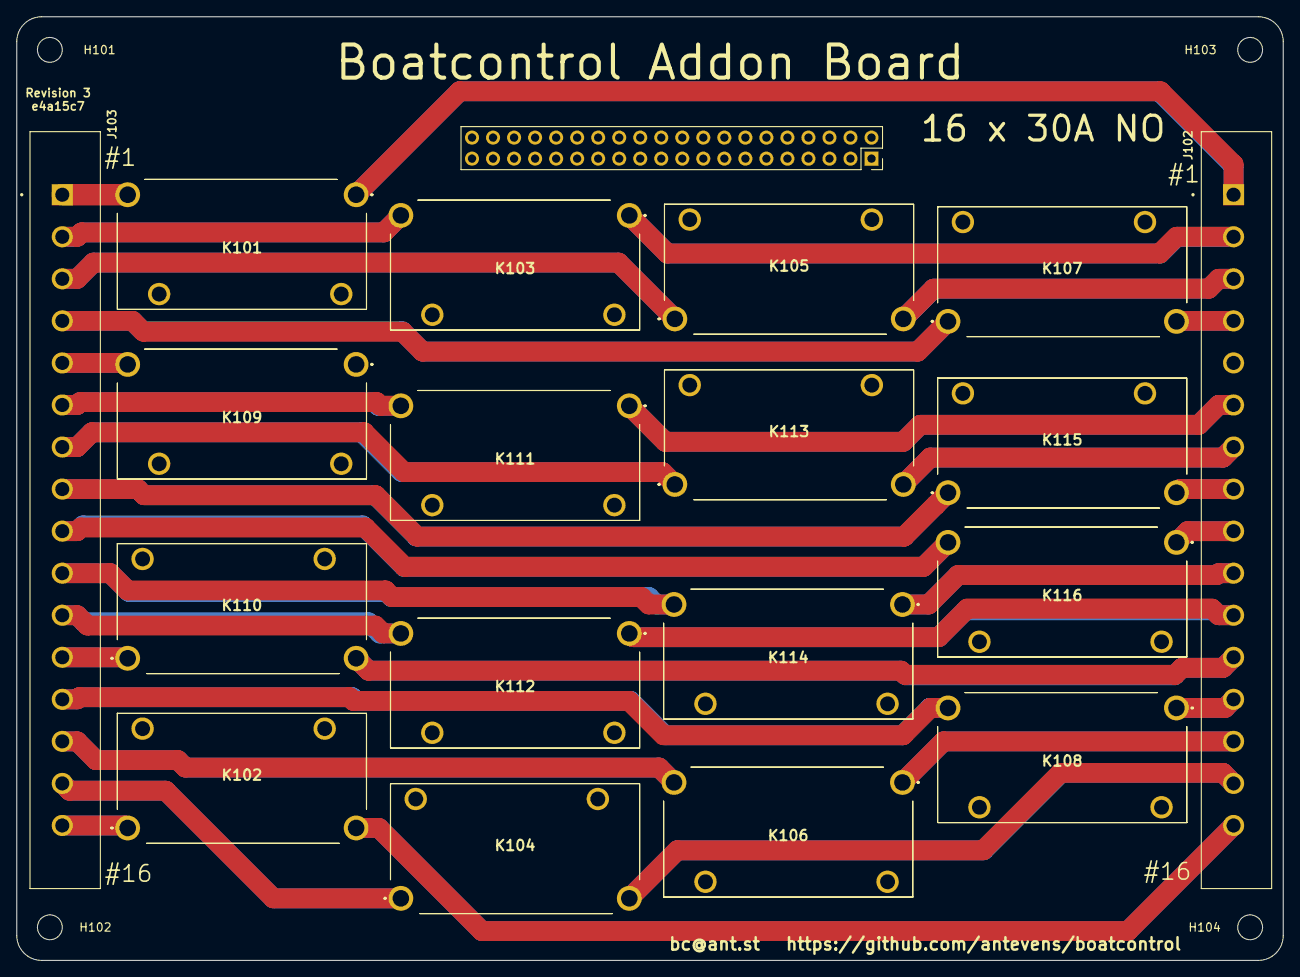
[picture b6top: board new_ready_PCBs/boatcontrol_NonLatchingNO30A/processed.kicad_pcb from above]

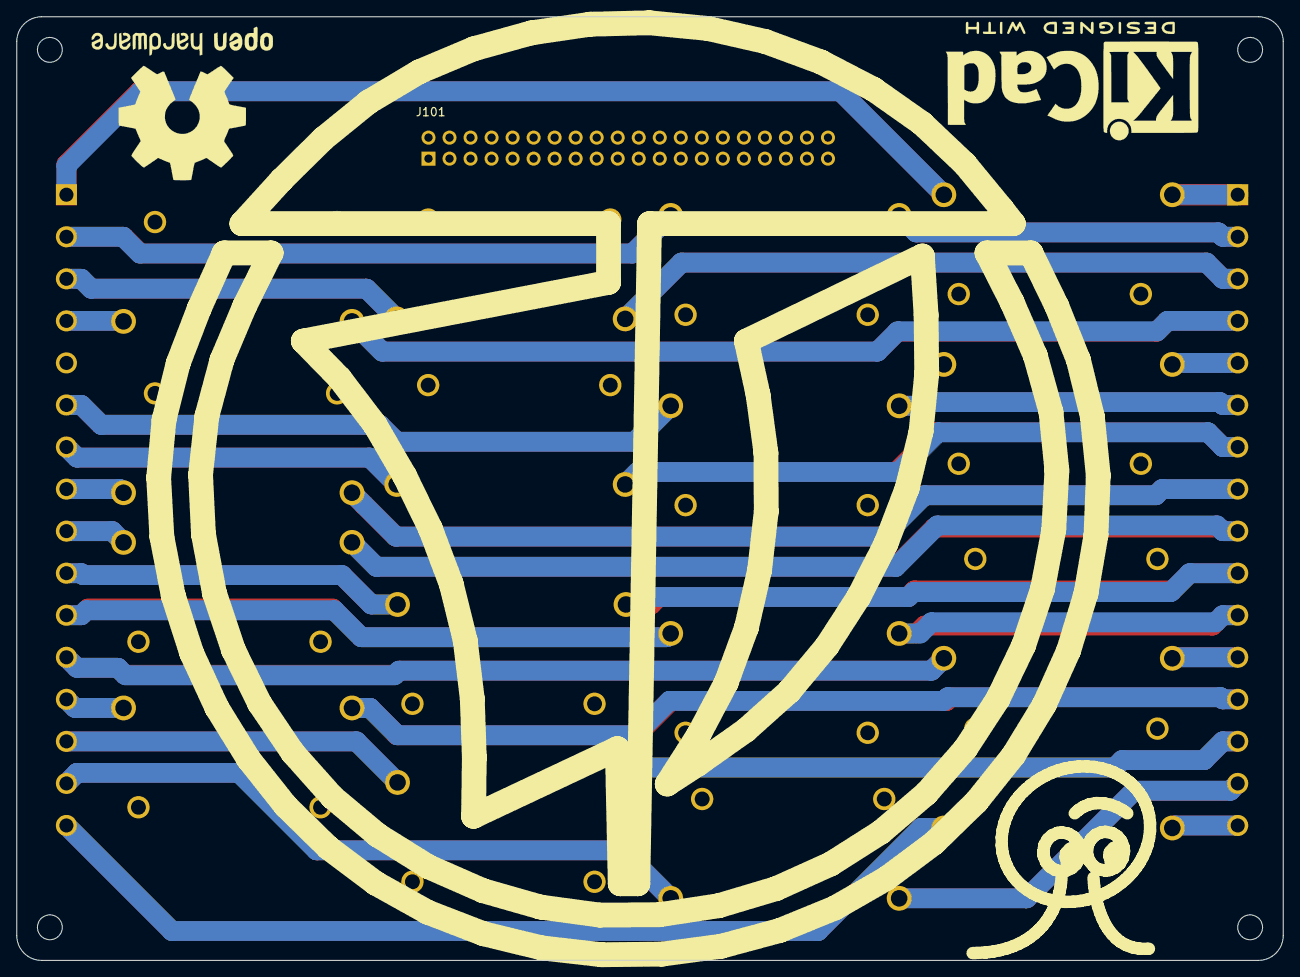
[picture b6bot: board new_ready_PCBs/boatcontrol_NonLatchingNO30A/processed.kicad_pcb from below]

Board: 4 copper layers, 153.0 x 114.0 mm, 27 parts (4 on the bottom side), 48 nets.

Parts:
G101: LOGO_RUGLUDALLUR; Rugludallur-Logo_SilkScreen
G102: LOGO_ANT; Ant_Logo_SilkScreen
H101, H102, H103, H104: MountingHole; MountingHole_3mm
J101: Conn_02x20_Odd_Even Header; PinSocket_2x20_P2.54mm_Vertical
J102, J103: TBP01R2W-508-16BE; CUI_TBP01R2W-508-16BE
K101, K102, K103, K104, K105, K106, K107, K108, K109, K110, K111, K112, K113, K114, K115, K116: ALFG2PF121
LOGO101: Logo_Open_Hardware_Large; KiCad-Logo2_12mm_SilkScreen
LOGO102: Logo_Open_Hardware_Large; OSHW-Logo2_24.3x20mm_SilkScreen

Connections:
/K1_COIL_ON: J101.1, J101.2, K101.4
/K2_COIL_ON: J101.3, J101.4, K103.4
/K3_COIL_ON: J101.5, J101.6, K105.3
/K4_COIL_ON: J101.7, J101.8, K107.3
/K5_COIL_ON: J101.9, J101.10, K109.4
/K6_COIL_ON: J101.11, J101.12, K111.4
/K7_COIL_ON: J101.13, J101.14, K113.3
/K8_COIL_ON: J101.15, J101.16, K115.3
/K9_COIL_ON: J101.17, J101.18, K116.4
/K10_COIL_ON: J101.19, J101.20, K114.4
/K11_COIL_ON: J101.21, J101.22, K112.4
/K12_COIL_ON: J101.23, J101.24, K110.3
/K13_COIL_ON: J101.25, J101.26, K108.4
/K14_COIL_ON: J101.27, J101.28, K106.4
/K15_COIL_ON: J101.29, J101.30, K104.3
/K16_COIL_ON: J101.31, J101.32, K102.3
GND: J101.33, J101.34, J101.35, J101.36, J101.37, J101.38, J101.39, J101.40, K101.3, K102.4, K103.3, K104.4, K105.4, K106.3, K107.4, K108.3, K109.3, K110.4, K111.3, K112.3, K113.4, K114.3, K115.4, K116.3
unnamed: J102.1, K101.1
unnamed: J102.2, K103.1
unnamed: J102.3, K105.2
unnamed: J102.4, K107.2
unnamed: J102.6, K111.1
unnamed: J102.7, K113.2
unnamed: J102.8, K115.2
unnamed: J102.9, K116.1
unnamed: J102.10, K114.1
unnamed: J102.11, K112.1
unnamed: J102.12, K110.2
unnamed: J102.13, K108.1
unnamed: J102.14, K106.1
unnamed: J102.15, K104.2
unnamed: J102.16, K102.2
unnamed: J103.1, K101.2
unnamed: J103.2, K103.2
unnamed: J103.3, K105.1
unnamed: J103.4, K107.1
unnamed: J103.5, K109.2
unnamed: J103.6, K111.2
unnamed: J103.7, K113.1
unnamed: J103.8, K115.1
unnamed: J103.9, K116.2
unnamed: J103.10, K114.2
unnamed: J103.11, K112.2
unnamed: J103.12, K110.1
unnamed: J103.13, K108.2
unnamed: J103.14, K106.2
unnamed: J103.15, K104.1
unnamed: J103.16, K102.1

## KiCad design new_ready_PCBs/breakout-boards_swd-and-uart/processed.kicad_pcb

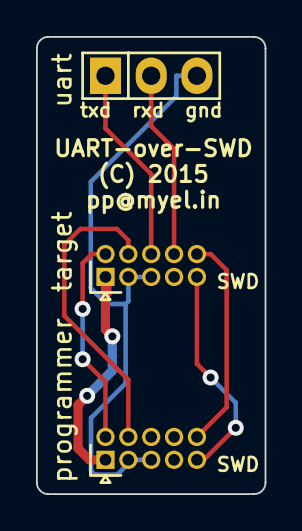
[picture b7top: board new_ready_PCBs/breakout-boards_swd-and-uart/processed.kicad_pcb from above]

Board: 2 copper layers, 12.7 x 25.4 mm, 3 parts (0 on the bottom side), 8 nets.

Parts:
P1: target; pin_array_5x2_50mil
P2: uart; Socket_Strip_Straight_1x03
P3: programmer; pin_array_5x2_50mil

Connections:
/GND: P1.3, P1.5, P2.3, P3.3, P3.5
/GND_DET: P1.9, P3.9
/RXD: P1.8, P2.2
/SWCLK: P1.4, P3.4
/SWDIO: P1.2, P3.2
/TXD: P1.6, P2.1
/VCC: P1.1, P3.1
/nRESET: P1.10, P3.10

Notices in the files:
new_ready_PCBs/bms-8s50-ic_bms-8s50-ic/processed.kicad_pcb:
License: CC-BY-SA
new_ready_PCBs/breakout-boards_swd-and-uart/processed.kicad_pcb:
(C) 2015
